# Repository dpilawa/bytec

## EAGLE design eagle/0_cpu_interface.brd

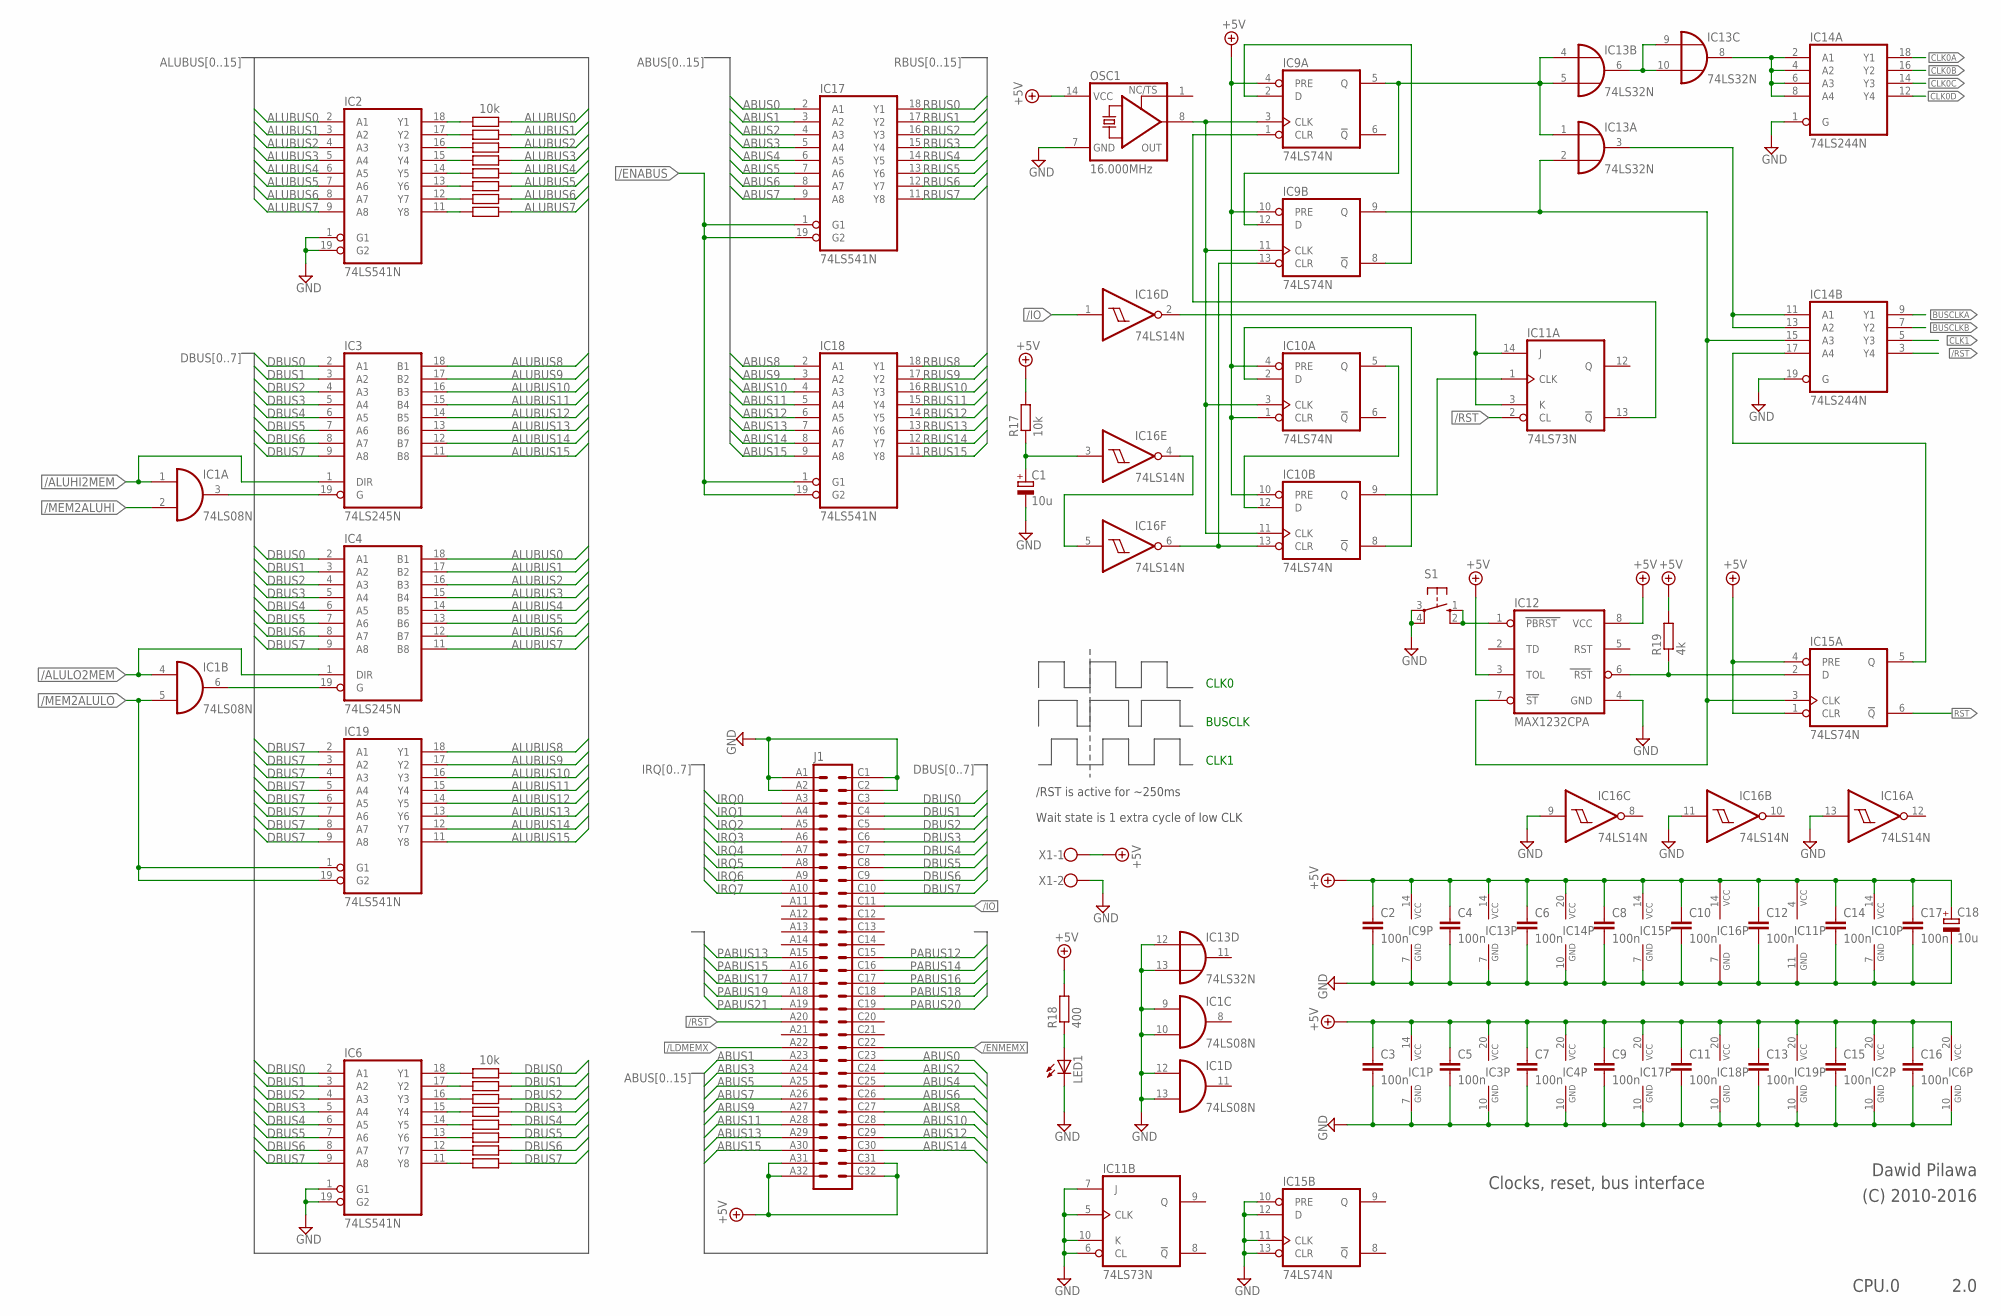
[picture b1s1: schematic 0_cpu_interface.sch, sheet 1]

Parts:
C1: 10u; E2,5-5
C2, C3, C4, C5, C6, C7, C8, C9, C10, C11, C12, C13, C14, C15, C16, C17: 100n; C050-024X044
C18: 10u; E2,5-6
IC1: 74LS08N; DIL14
IC2, IC6, IC17, IC18, IC19: 74LS541N; DIL20
IC3, IC4: 74LS245N; DIL20
IC9, IC10, IC15: 74LS74N; DIL14
IC11: 74LS73N; DIL14
IC12: MAX1232CPA; DIL08
IC13: 74LS32N; DIL14
IC14: 74LS244N; DIL20
IC16: 74LS14N; DIL14
J1: VG64B
LED1: LED5MM
OSC1: 16.000MHz; DIL14S
R1, R9, R17: 10k; 0204/7
R2, R3, R4, R5, R6, R7, R8, R10, R11, R12, R13, R14, R15, R16: R-EU_0204/7; 0204/7
R18: 400; 0204/7
R19: 4k; 0204/7
S1: 10-XX; B3F-10XX
X1: W237-102

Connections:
+5V: C2.1, C3.1, C4.1, C5.1, C6.1, C7.1, C8.1, C9.1, C10.1, C11.1, C12.1, C13.1, C14.1, C15.1, C16.1, C17.1, C18.+, IC1.14 (VCC), IC2.20 (VCC), IC3.20 (VCC), IC4.20 (VCC), IC6.20 (VCC), IC9.4 (PRE), IC9.10 (PRE), IC9.14 (VCC), IC10.1 (CLR), IC10.4 (PRE), IC10.10 (PRE), IC10.14 (VCC), IC11.4 (VCC), IC12.3 (TOL), IC12.8 (VCC), IC13.14 (VCC), IC14.20 (VCC), IC15.1 (CLR), IC15.4 (PRE), IC15.14 (VCC), IC16.14 (VCC), IC17.20 (VCC), IC18.20 (VCC), IC19.20 (VCC), J1.A31, J1.A32, J1.C31, J1.C32, OSC1.14 (VCC), R17.2, R18.2, R19.2, X1.1; also elsewhere on the board
/ALUHI2MEM: IC1.1 (I0), IC3.1 (DIR); also elsewhere on the board
/ALULO2MEM: IC1.4 (I0), IC4.1 (DIR); also elsewhere on the board
/ENABUS: IC17.1 (G1), IC17.19 (G2), IC18.1 (G1), IC18.19 (G2); also elsewhere on the board
/ENMEMX: J1.C22; also elsewhere on the board
/IO: IC16.1 (I), J1.C11; also elsewhere on the board
/LDMEMX: J1.A22; also elsewhere on the board
/MEM2ALUHI: IC1.2 (I1); also elsewhere on the board
/MEM2ALULO: IC1.5 (I1), IC19.1 (G1), IC19.19 (G2); also elsewhere on the board
/RST: IC11.2 (CL), IC14.3 (Y4), J1.A20; also elsewhere on the board
ABUS0: IC17.2 (A1), J1.C23; also elsewhere on the board
ABUS1: IC17.3 (A2), J1.A23; also elsewhere on the board
ABUS2: IC17.4 (A3), J1.C24; also elsewhere on the board
ABUS3: IC17.5 (A4), J1.A24; also elsewhere on the board
ABUS4: IC17.6 (A5), J1.C25; also elsewhere on the board
ABUS5: IC17.7 (A6), J1.A25; also elsewhere on the board
ABUS6: IC17.8 (A7), J1.C26; also elsewhere on the board
ABUS7: IC17.9 (A8), J1.A26; also elsewhere on the board
ABUS8: IC18.2 (A1), J1.C27; also elsewhere on the board
ABUS9: IC18.3 (A2), J1.A27; also elsewhere on the board
ABUS10: IC18.4 (A3), J1.C28; also elsewhere on the board
ABUS11: IC18.5 (A4), J1.A28; also elsewhere on the board
ABUS12: IC18.6 (A5), J1.C29; also elsewhere on the board
ABUS13: IC18.7 (A6), J1.A29; also elsewhere on the board
ABUS14: IC18.8 (A7), J1.C30; also elsewhere on the board
ABUS15: IC18.9 (A8), J1.A30; also elsewhere on the board
ALUBUS0: IC2.2 (A1), IC4.18 (B1), R1.2; also elsewhere on the board
ALUBUS1: IC2.3 (A2), IC4.17 (B2), R2.2; also elsewhere on the board
ALUBUS2: IC2.4 (A3), IC4.16 (B3), R3.2; also elsewhere on the board
ALUBUS3: IC2.5 (A4), IC4.15 (B4), R4.2; also elsewhere on the board
ALUBUS4: IC2.6 (A5), IC4.14 (B5), R5.2; also elsewhere on the board
ALUBUS5: IC2.7 (A6), IC4.13 (B6), R6.2; also elsewhere on the board
ALUBUS6: IC2.8 (A7), IC4.12 (B7), R7.2; also elsewhere on the board
ALUBUS7: IC2.9 (A8), IC4.11 (B8), R8.2; also elsewhere on the board
ALUBUS8: IC3.18 (B1), IC19.18 (Y1); also elsewhere on the board
ALUBUS9: IC3.17 (B2), IC19.17 (Y2); also elsewhere on the board
ALUBUS10: IC3.16 (B3), IC19.16 (Y3); also elsewhere on the board
ALUBUS11: IC3.15 (B4), IC19.15 (Y4); also elsewhere on the board
ALUBUS12: IC3.14 (B5), IC19.14 (Y5); also elsewhere on the board
ALUBUS13: IC3.13 (B6), IC19.13 (Y6); also elsewhere on the board
ALUBUS14: IC3.12 (B7), IC19.12 (Y7); also elsewhere on the board
ALUBUS15: IC3.11 (B8), IC19.11 (Y8); also elsewhere on the board
BUSCLK: IC13.3 (O), IC14.11 (A1), IC14.13 (A2)
BUSCLKA: IC14.9 (Y1); also elsewhere on the board
BUSCLKB: IC14.7 (Y2); also elsewhere on the board
CLK0: IC9.5 (Q), IC9.12 (D), IC13.1 (I0), IC13.4 (I0), IC13.5 (I1)
CLK0A: IC14.18 (Y1); also elsewhere on the board
CLK0B: IC14.16 (Y2); also elsewhere on the board
CLK0C: IC14.14 (Y3); also elsewhere on the board
CLK0D: IC14.12 (Y4); also elsewhere on the board
CLK1: IC14.5 (Y3); also elsewhere on the board
DBUS0: IC3.2 (A1), IC4.2 (A1), IC6.2 (A1), J1.C3, R9.2; also elsewhere on the board
DBUS1: IC3.3 (A2), IC4.3 (A2), IC6.3 (A2), J1.C4, R10.2; also elsewhere on the board
DBUS2: IC3.4 (A3), IC4.4 (A3), IC6.4 (A3), J1.C5, R11.2; also elsewhere on the board
DBUS3: IC3.5 (A4), IC4.5 (A4), IC6.5 (A4), J1.C6, R12.2; also elsewhere on the board
DBUS4: IC3.6 (A5), IC4.6 (A5), IC6.6 (A5), J1.C7, R13.2; also elsewhere on the board
DBUS5: IC3.7 (A6), IC4.7 (A6), IC6.7 (A6), J1.C8, R14.2; also elsewhere on the board
DBUS6: IC3.8 (A7), IC4.8 (A7), IC6.8 (A7), J1.C9, R15.2; also elsewhere on the board
DBUS7: IC3.9 (A8), IC4.9 (A8), IC6.9 (A8), IC19.2 (A1), IC19.3 (A2), IC19.4 (A3), IC19.5 (A4), IC19.6 (A5), IC19.7 (A6), IC19.8 (A7), IC19.9 (A8), J1.C10, R16.2; also elsewhere on the board
GND: C1.-, C2.2, C3.2, C4.2, C5.2, C6.2, C7.2, C8.2, C9.2, C10.2, C11.2, C12.2, C13.2, C14.2, C15.2, C16.2, C17.2, C18.-, IC1.7 (GND), IC1.9 (I0), IC1.10 (I1), IC1.12 (I0), IC1.13 (I1), IC2.1 (G1), IC2.10 (GND), IC2.19 (G2), IC3.10 (GND), IC4.10 (GND), IC6.1 (G1), IC6.10 (GND), IC6.19 (G2), IC9.7 (GND), IC10.7 (GND), IC11.5 (CLK), IC11.6 (CL), IC11.7 (J), IC11.10 (K), IC11.11 (GND), IC12.4 (GND), IC13.7 (GND), IC13.12 (I0), IC13.13 (I1), IC14.1 (G), IC14.10 (GND), IC14.19 (G), IC15.7 (GND), IC15.10 (PRE), IC15.11 (CLK), IC15.12 (D), IC15.13 (CLR), IC16.7 (GND), IC16.9 (I), IC16.11 (I), IC16.13 (I), IC17.10 (GND), IC18.10 (GND), IC19.10 (GND), J1.A1, J1.A2, J1.C1, J1.C2, LED1.K (C), OSC1.7 (GND), S1.3, S1.4 (P1), X1.2; also elsewhere on the board
IRQ0: J1.A3; also elsewhere on the board
IRQ1: J1.A4; also elsewhere on the board
IRQ2: J1.A5; also elsewhere on the board
IRQ3: J1.A6; also elsewhere on the board
IRQ4: J1.A7; also elsewhere on the board
IRQ5: J1.A8; also elsewhere on the board
IRQ6: J1.A9; also elsewhere on the board
IRQ7: J1.A10; also elsewhere on the board
unnamed: IC1.3 (O), IC3.19 (G)
unnamed: IC1.6 (O), IC4.19 (G)
unnamed: IC2.18 (Y1), R1.1
unnamed: IC2.17 (Y2), R2.1
unnamed: IC2.16 (Y3), R3.1
unnamed: IC2.15 (Y4), R4.1
unnamed: IC2.14 (Y5), R5.1
unnamed: IC2.13 (Y6), R6.1
unnamed: IC2.12 (Y7), R7.1
unnamed: IC2.11 (Y8), R8.1
unnamed: IC6.18 (Y1), R9.1
unnamed: IC6.17 (Y2), R10.1
unnamed: IC6.16 (Y3), R11.1
unnamed: IC6.15 (Y4), R12.1
unnamed: IC6.14 (Y5), R13.1
unnamed: IC6.12 (Y7), R15.1
unnamed: IC6.11 (Y8), R16.1
unnamed: IC6.13 (Y6), R14.1
unnamed: IC12.1 (PBRST), S1.1 (S), S1.2 (S1)
unnamed: IC9.3 (CLK), IC9.11 (CLK), IC10.3 (CLK), IC10.11 (CLK), OSC1.8 (OUT)
unnamed: LED1.A, R18.1
unnamed: IC9.2 (D), IC9.8 (!Q)
unnamed: IC14.17 (A4), IC15.5 (Q)
unnamed: IC12.6 (RST), IC15.2 (D), R19.1
unnamed: IC10.2 (D), IC10.8 (!Q)
unnamed: IC13.8 (O), IC14.2 (A1), IC14.4 (A2), IC14.6 (A3), IC14.8 (A4)
unnamed: IC9.1 (CLR), IC11.13 (!Q)
unnamed: C1.+, IC16.3 (I), R17.1
unnamed: IC13.6 (O), IC13.9 (I0), IC13.10 (I1)
unnamed: IC9.9 (Q), IC12.7 (ST), IC13.2 (I1), IC14.15 (A3), IC15.3 (CLK)
unnamed: IC10.5 (Q), IC10.12 (D)
unnamed: IC10.9 (Q), IC11.1 (CLK)
unnamed: IC11.3 (K), IC11.14 (J), IC16.2 (O)
unnamed: IC16.4 (O), IC16.5 (I)
unnamed: IC9.13 (CLR), IC10.13 (CLR), IC16.6 (O)
PABUS12: J1.C15; also elsewhere on the board
PABUS13: J1.A15; also elsewhere on the board
PABUS14: J1.C16; also elsewhere on the board
PABUS15: J1.A16; also elsewhere on the board
PABUS16: J1.C17; also elsewhere on the board
PABUS17: J1.A17; also elsewhere on the board
PABUS18: J1.C18; also elsewhere on the board
PABUS19: J1.A18; also elsewhere on the board
PABUS20: J1.C19; also elsewhere on the board
PABUS21: J1.A19; also elsewhere on the board
RBUS0: IC17.18 (Y1); also elsewhere on the board
RBUS1: IC17.17 (Y2); also elsewhere on the board
RBUS2: IC17.16 (Y3); also elsewhere on the board
RBUS3: IC17.15 (Y4); also elsewhere on the board
RBUS4: IC17.14 (Y5); also elsewhere on the board
RBUS5: IC17.13 (Y6); also elsewhere on the board
RBUS6: IC17.12 (Y7); also elsewhere on the board
RBUS7: IC17.11 (Y8); also elsewhere on the board
RBUS8: IC18.18 (Y1); also elsewhere on the board
RBUS9: IC18.17 (Y2); also elsewhere on the board
RBUS10: IC18.16 (Y3); also elsewhere on the board
RBUS11: IC18.15 (Y4); also elsewhere on the board
RBUS12: IC18.14 (Y5); also elsewhere on the board
RBUS13: IC18.13 (Y6); also elsewhere on the board
RBUS14: IC18.12 (Y7); also elsewhere on the board
RBUS15: IC18.11 (Y8); also elsewhere on the board
RST: IC15.6 (!Q); also elsewhere on the board

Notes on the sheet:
Clocks, reset, bus interface
Dawid Pilawa
(C) 2010-2016
CPU.0
2.0
/RST is active for ~250ms
CLK0
BUSCLK
CLK1
Wait state is 1 extra cycle of low CLK

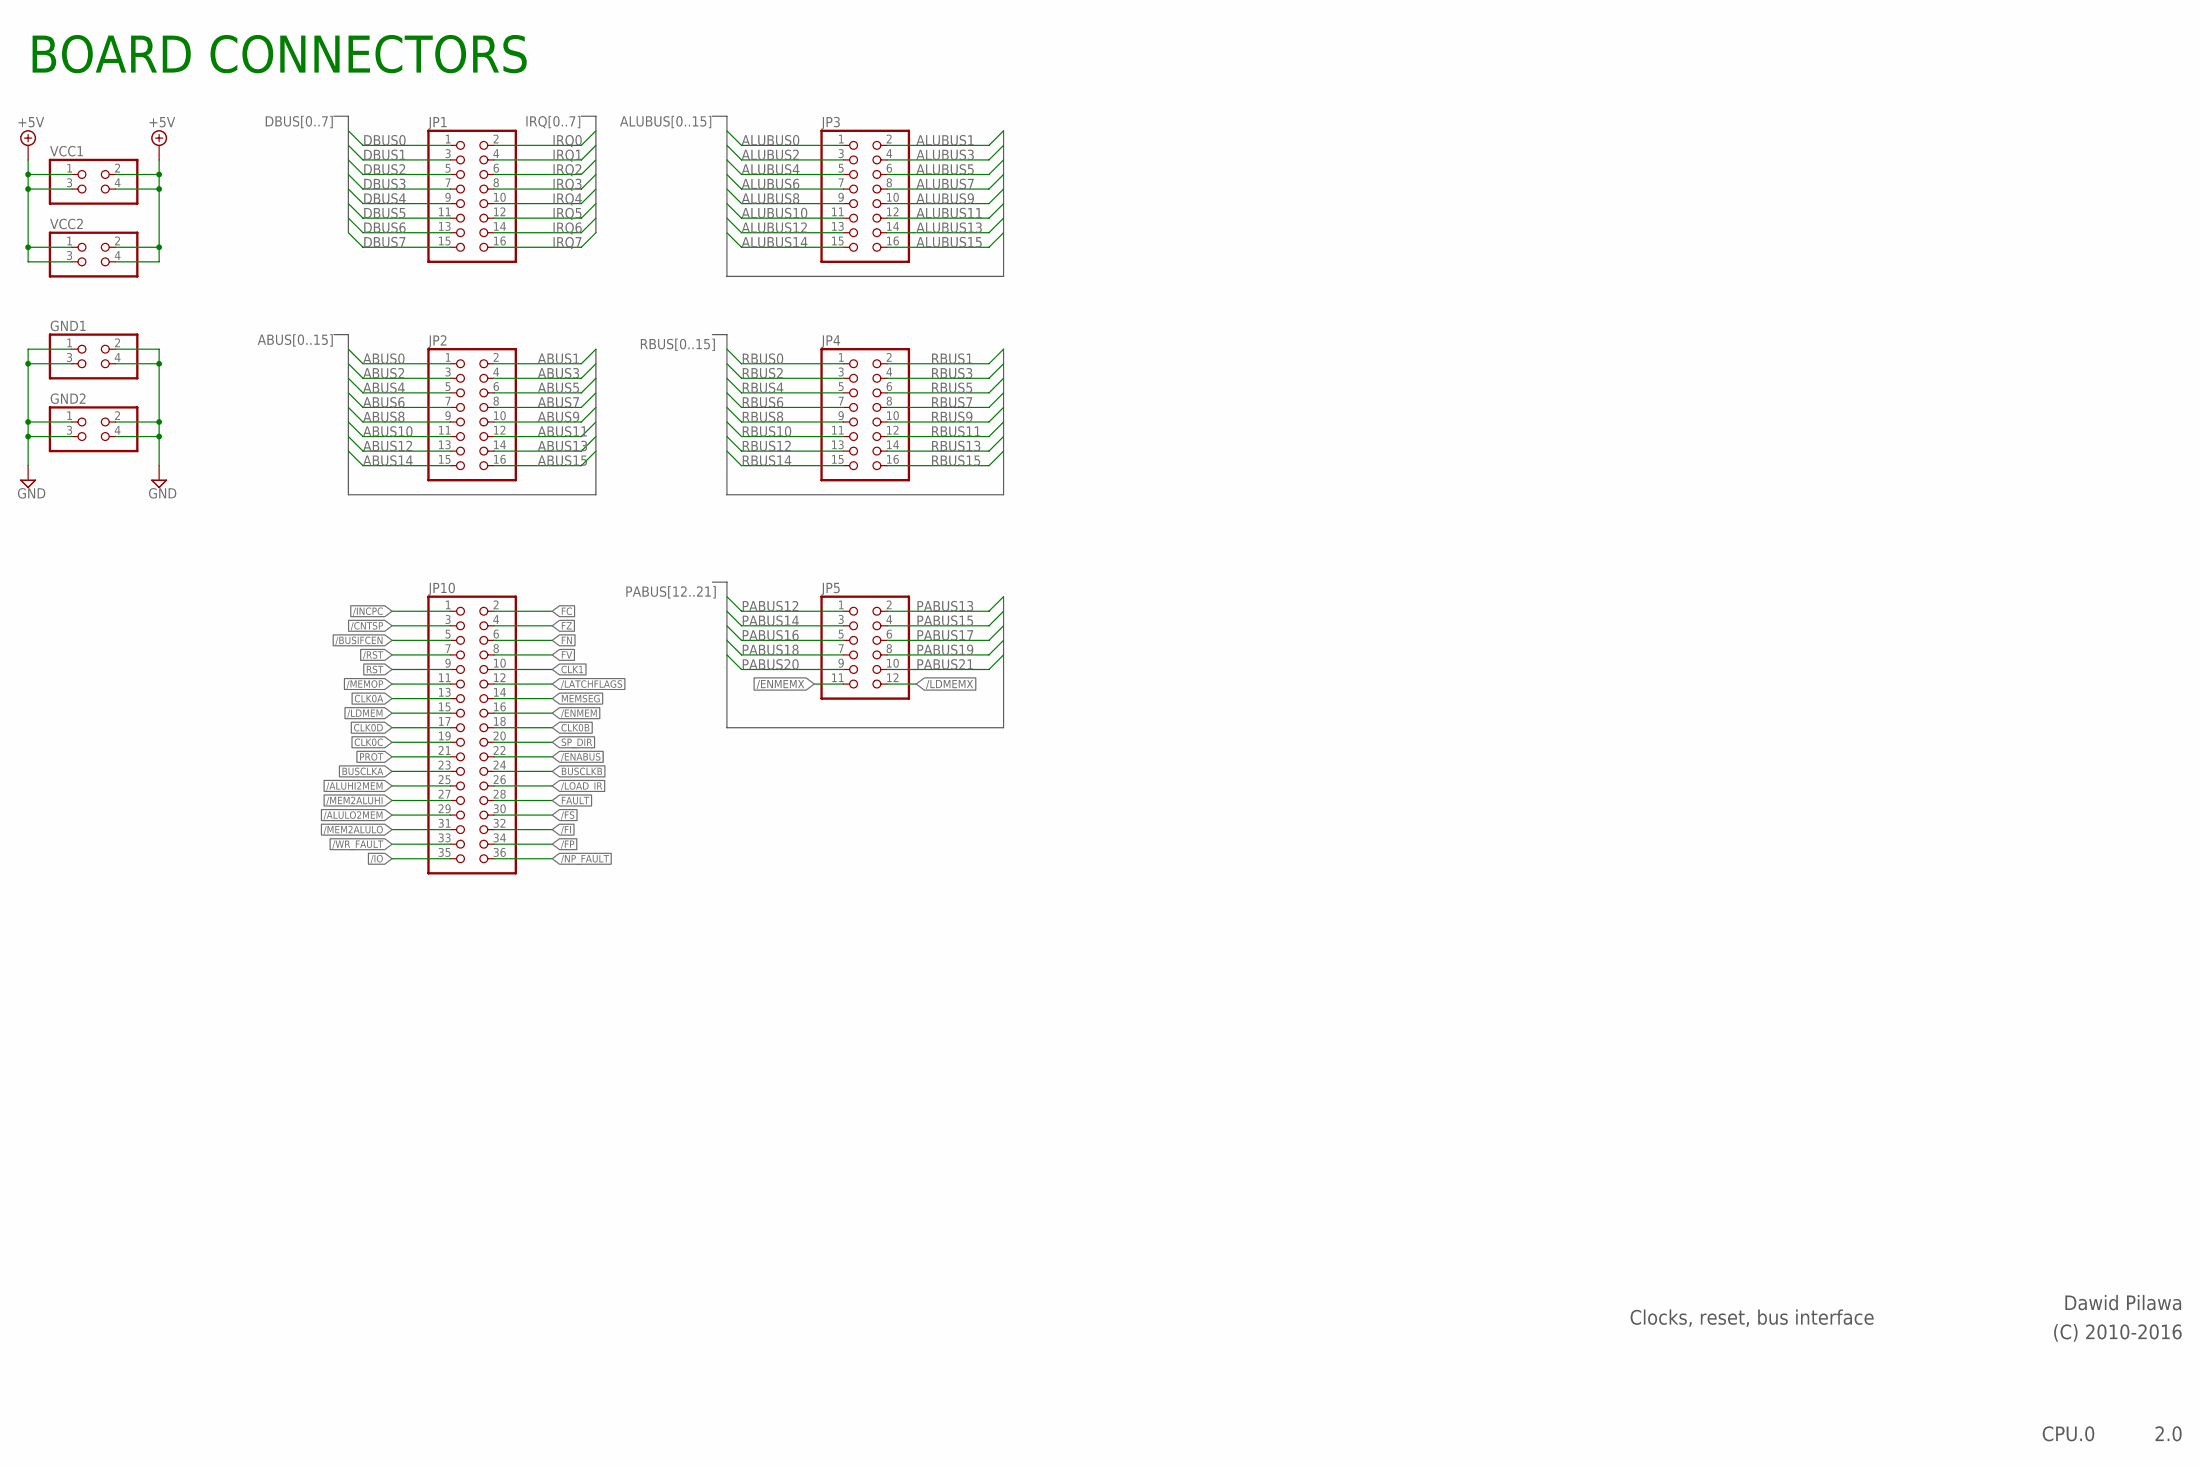
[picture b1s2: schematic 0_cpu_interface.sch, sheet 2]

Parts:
GND1, GND2: PINHD-2X2; 2X02
JP1, JP2, JP3, JP4: PINHD-2X8; 2X08
JP5: PINHD-2X6; 2X06
JP10: PINHD-2X18; 2X18
VCC1, VCC2: PINHD-2X2; 2X02

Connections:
+5V: VCC1.1, VCC1.2, VCC1.3, VCC1.4, VCC2.1, VCC2.2, VCC2.3, VCC2.4; also elsewhere on the board
/ALUHI2MEM: JP10.25; also elsewhere on the board
/ALULO2MEM: JP10.29; also elsewhere on the board
/BUSIFCEN: JP10.5
/CNTSP: JP10.3
/ENABUS: JP10.22; also elsewhere on the board
/ENMEM: JP10.16
/ENMEMX: JP5.11; also elsewhere on the board
/FI: JP10.32
/FP: JP10.34
/FS: JP10.30
/INCPC: JP10.1
/IO: JP10.35; also elsewhere on the board
/LATCHFLAGS: JP10.12
/LDMEM: JP10.15
/LDMEMX: JP5.12; also elsewhere on the board
/LOAD_IR: JP10.26
/MEM2ALUHI: JP10.27; also elsewhere on the board
/MEM2ALULO: JP10.31; also elsewhere on the board
/MEMOP: JP10.11
/NP_FAULT: JP10.36
/RST: JP10.7; also elsewhere on the board
/WR_FAULT: JP10.33
ABUS0: JP2.1; also elsewhere on the board
ABUS1: JP2.2; also elsewhere on the board
ABUS2: JP2.3; also elsewhere on the board
ABUS3: JP2.4; also elsewhere on the board
ABUS4: JP2.5; also elsewhere on the board
ABUS5: JP2.6; also elsewhere on the board
ABUS6: JP2.7; also elsewhere on the board
ABUS7: JP2.8; also elsewhere on the board
ABUS8: JP2.9; also elsewhere on the board
ABUS9: JP2.10; also elsewhere on the board
ABUS10: JP2.11; also elsewhere on the board
ABUS11: JP2.12; also elsewhere on the board
ABUS12: JP2.13; also elsewhere on the board
ABUS13: JP2.14; also elsewhere on the board
ABUS14: JP2.15; also elsewhere on the board
ABUS15: JP2.16; also elsewhere on the board
ALUBUS0: JP3.1; also elsewhere on the board
ALUBUS1: JP3.2; also elsewhere on the board
ALUBUS2: JP3.3; also elsewhere on the board
ALUBUS3: JP3.4; also elsewhere on the board
ALUBUS4: JP3.5; also elsewhere on the board
ALUBUS5: JP3.6; also elsewhere on the board
ALUBUS6: JP3.7; also elsewhere on the board
ALUBUS7: JP3.8; also elsewhere on the board
ALUBUS8: JP3.9; also elsewhere on the board
ALUBUS9: JP3.10; also elsewhere on the board
ALUBUS10: JP3.11; also elsewhere on the board
ALUBUS11: JP3.12; also elsewhere on the board
ALUBUS12: JP3.13; also elsewhere on the board
ALUBUS13: JP3.14; also elsewhere on the board
ALUBUS14: JP3.15; also elsewhere on the board
ALUBUS15: JP3.16; also elsewhere on the board
BUSCLKA: JP10.23; also elsewhere on the board
BUSCLKB: JP10.24; also elsewhere on the board
CLK0A: JP10.13; also elsewhere on the board
CLK0B: JP10.18; also elsewhere on the board
CLK0C: JP10.19; also elsewhere on the board
CLK0D: JP10.17; also elsewhere on the board
CLK1: JP10.10; also elsewhere on the board
DBUS0: JP1.1; also elsewhere on the board
DBUS1: JP1.3; also elsewhere on the board
DBUS2: JP1.5; also elsewhere on the board
DBUS3: JP1.7; also elsewhere on the board
DBUS4: JP1.9; also elsewhere on the board
DBUS5: JP1.11; also elsewhere on the board
DBUS6: JP1.13; also elsewhere on the board
DBUS7: JP1.15; also elsewhere on the board
FAULT: JP10.28
FC: JP10.2
FN: JP10.6
FV: JP10.8
FZ: JP10.4
GND: GND1.1, GND1.2, GND1.3, GND1.4, GND2.1, GND2.2, GND2.3, GND2.4; also elsewhere on the board
IRQ0: JP1.2; also elsewhere on the board
IRQ1: JP1.4; also elsewhere on the board
IRQ2: JP1.6; also elsewhere on the board
IRQ3: JP1.8; also elsewhere on the board
IRQ4: JP1.10; also elsewhere on the board
IRQ5: JP1.12; also elsewhere on the board
IRQ6: JP1.14; also elsewhere on the board
IRQ7: JP1.16; also elsewhere on the board
MEMSEG: JP10.14
PABUS12: JP5.1; also elsewhere on the board
PABUS13: JP5.2; also elsewhere on the board
PABUS14: JP5.3; also elsewhere on the board
PABUS15: JP5.4; also elsewhere on the board
PABUS16: JP5.5; also elsewhere on the board
PABUS17: JP5.6; also elsewhere on the board
PABUS18: JP5.7; also elsewhere on the board
PABUS19: JP5.8; also elsewhere on the board
PABUS20: JP5.9; also elsewhere on the board
PABUS21: JP5.10; also elsewhere on the board
PROT: JP10.21
RBUS0: JP4.1; also elsewhere on the board
RBUS1: JP4.2; also elsewhere on the board
RBUS2: JP4.3; also elsewhere on the board
RBUS3: JP4.4; also elsewhere on the board
RBUS4: JP4.5; also elsewhere on the board
RBUS5: JP4.6; also elsewhere on the board
RBUS6: JP4.7; also elsewhere on the board
RBUS7: JP4.8; also elsewhere on the board
RBUS8: JP4.9; also elsewhere on the board
RBUS9: JP4.10; also elsewhere on the board
RBUS10: JP4.11; also elsewhere on the board
RBUS11: JP4.12; also elsewhere on the board
RBUS12: JP4.13; also elsewhere on the board
RBUS13: JP4.14; also elsewhere on the board
RBUS14: JP4.15; also elsewhere on the board
RBUS15: JP4.16; also elsewhere on the board
RST: JP10.9; also elsewhere on the board
SP_DIR: JP10.20

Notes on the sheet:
Clocks, reset, bus interface
Dawid Pilawa
(C) 2010-2016
CPU.0
2.0
BOARD CONNECTORS

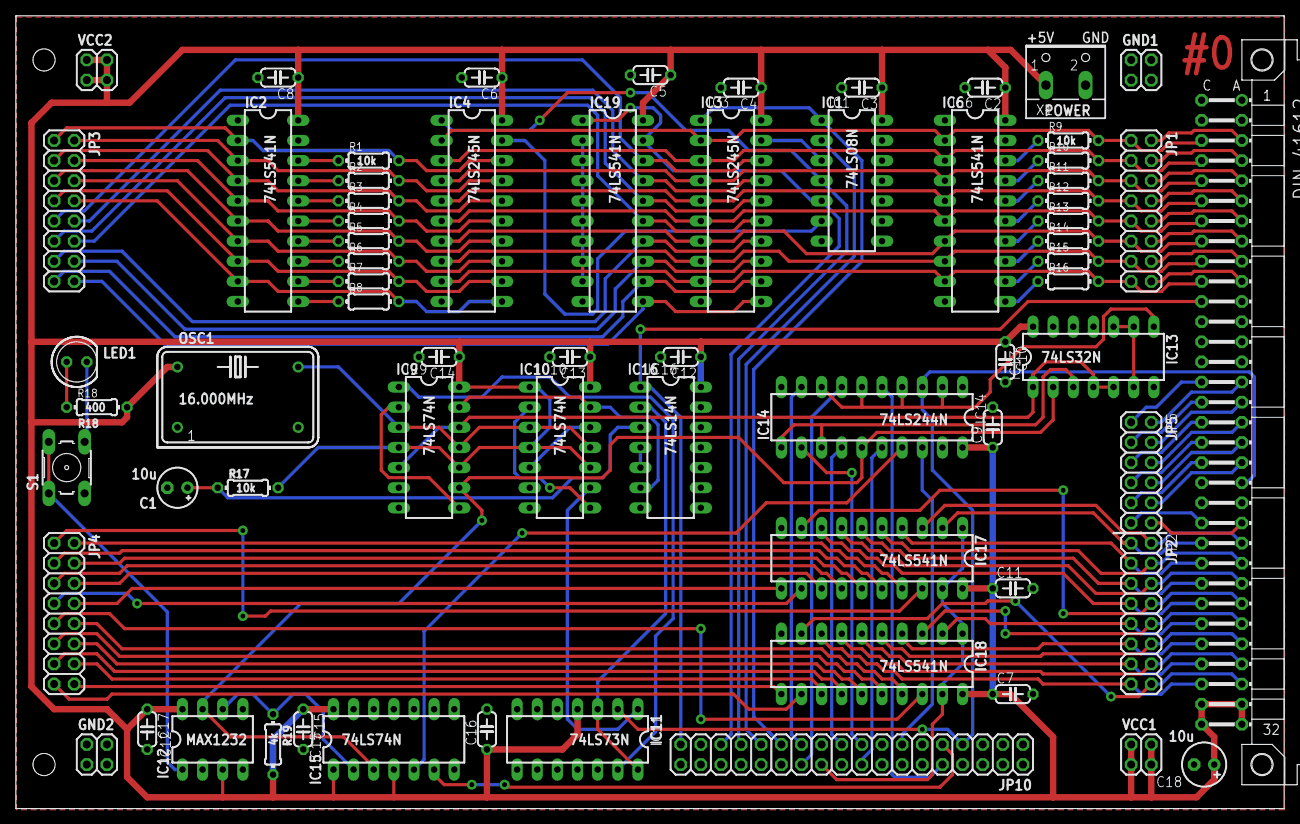
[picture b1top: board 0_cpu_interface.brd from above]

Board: 2 copper layers, 160.0 x 100.0 mm, 68 parts (0 on the bottom side), 130 nets.

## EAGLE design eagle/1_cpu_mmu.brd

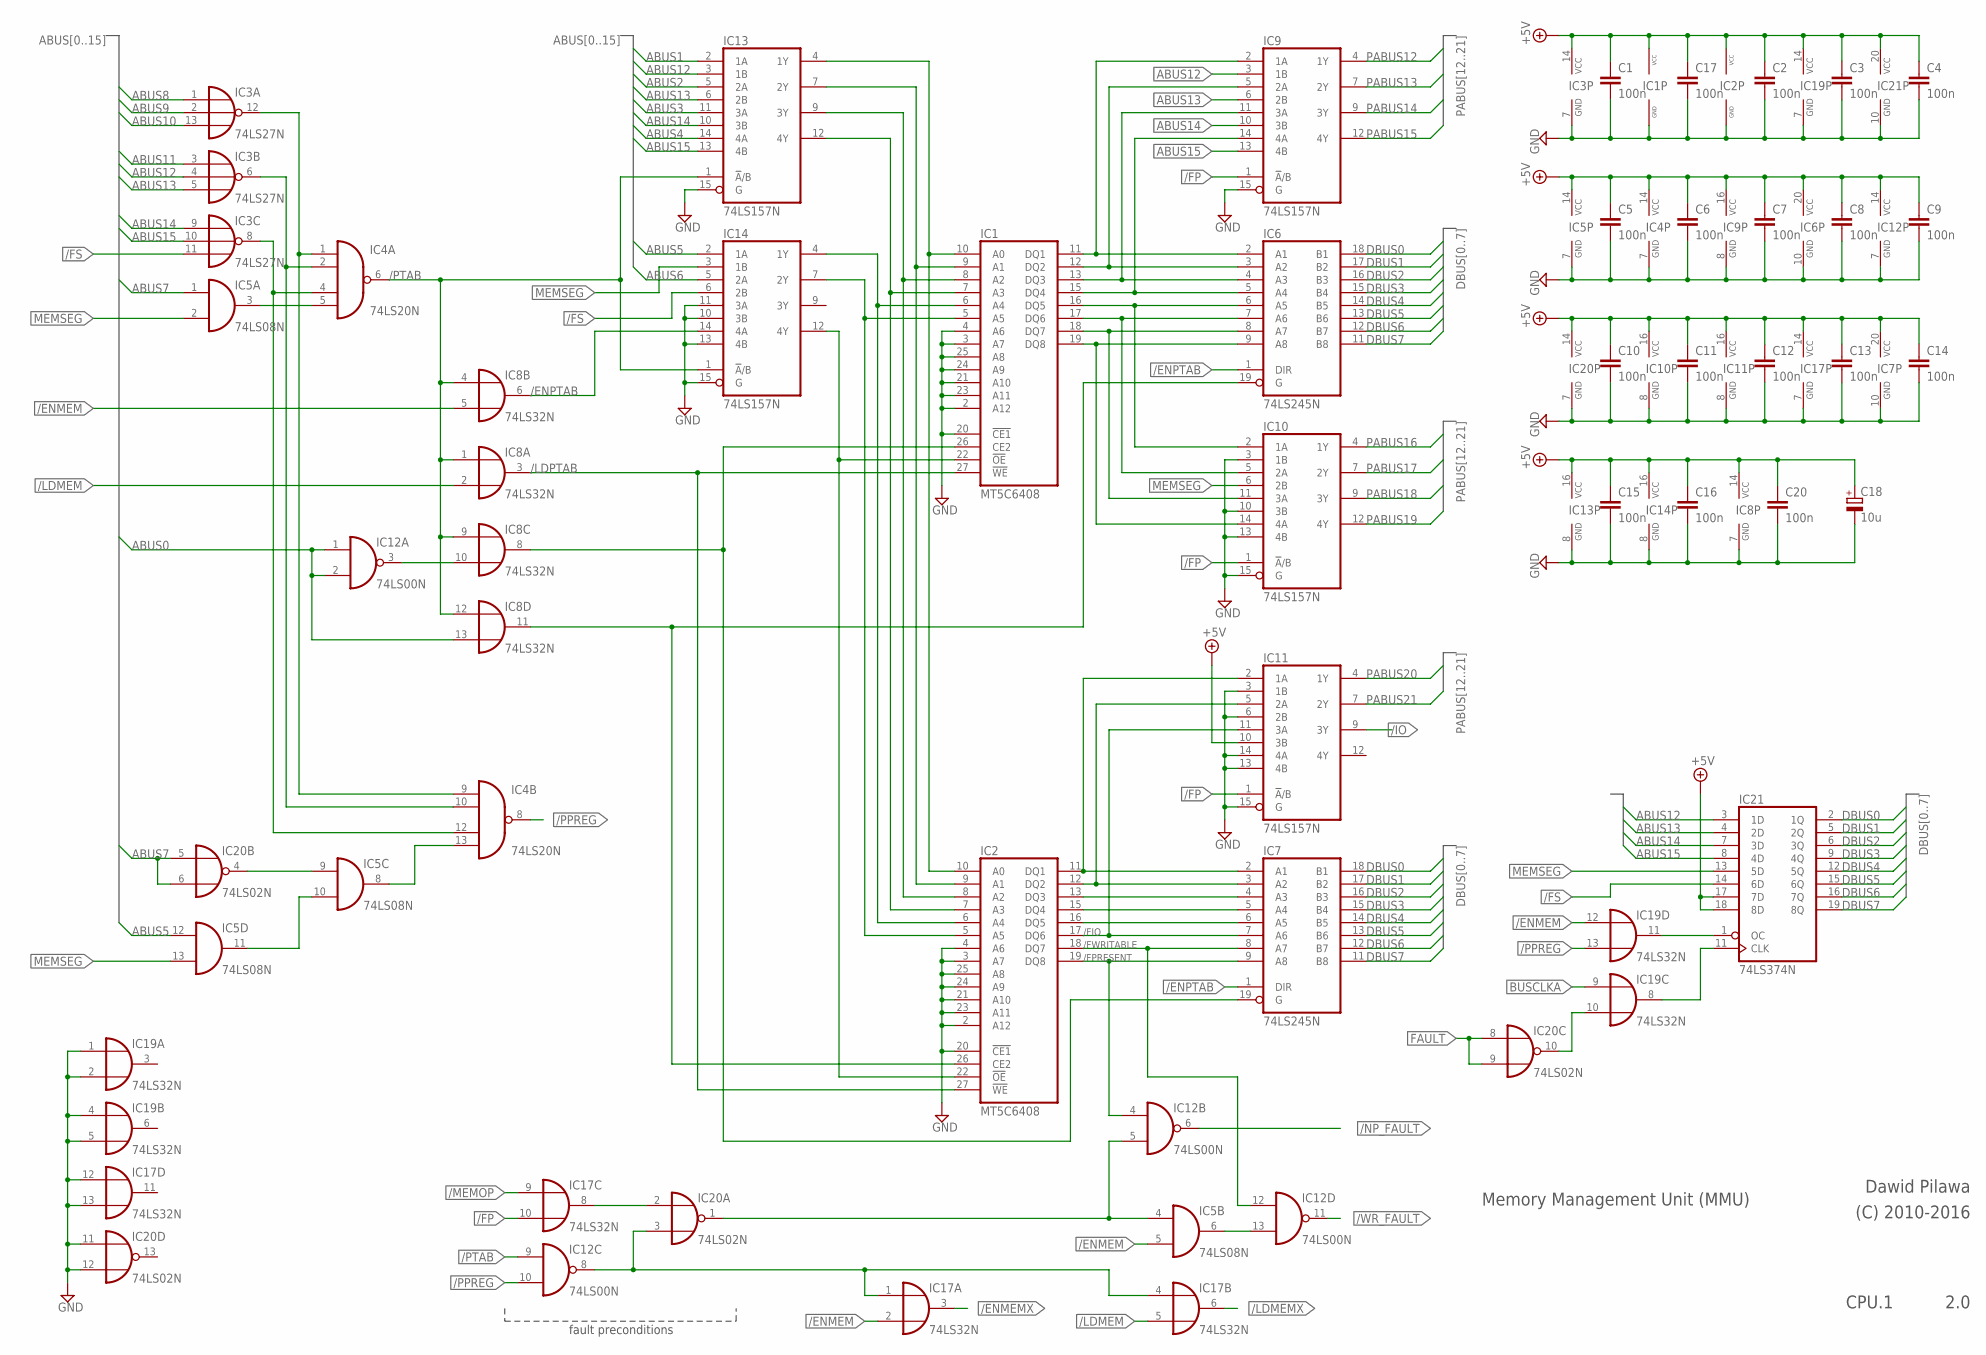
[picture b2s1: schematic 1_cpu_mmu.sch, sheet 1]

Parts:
C1, C2, C3, C4, C5, C6, C7, C8, C9, C10, C11, C12, C13, C14, C15, C16, C17, C20: 100n; C050-024X044
C18: 10u; E2,5-6
IC1, IC2: MT5C6408; DIL28-3
IC3: 74LS27N; DIL14
IC4: 74LS20N; DIL14
IC5: 74LS08N; DIL14
IC6, IC7: 74LS245N; DIL20
IC8, IC17, IC19: 74LS32N; DIL14
IC9, IC10, IC11, IC13, IC14: 74LS157N; DIL16
IC12: 74LS00N; DIL14
IC20: 74LS02N; DIL14
IC21: 74LS374N; DIL20

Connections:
+5V: C1.1, C2.1, C3.1, C4.1, C5.1, C6.1, C7.1, C8.1, C9.1, C10.1, C11.1, C12.1, C13.1, C14.1, C15.1, C16.1, C17.1, C18.+, C20.1, IC1.28 (VCC), IC2.28 (VCC), IC3.14 (VCC), IC4.14 (VCC), IC5.14 (VCC), IC6.20 (VCC), IC7.20 (VCC), IC8.14 (VCC), IC9.16 (VCC), IC10.16 (VCC), IC11.10 (3B), IC11.16 (VCC), IC12.14 (VCC), IC13.16 (VCC), IC14.16 (VCC), IC17.14 (VCC), IC19.14 (VCC), IC20.14 (VCC), IC21.17 (7D), IC21.18 (8D), IC21.20 (VCC); also elsewhere on the board
/ENMEM: IC5.5 (I1), IC8.5 (I1), IC17.2 (I1), IC19.12 (I0); also elsewhere on the board
/ENMEMX: IC17.3 (O); also elsewhere on the board
/ENPTAB: IC6.1 (DIR), IC7.1 (DIR), IC8.6 (O), IC14.14 (4A)
/FIO: IC2.17 (DQ6), IC7.7 (A6), IC11.11 (3A)
/FP: IC9.1 (!A!/B), IC10.1 (!A!/B), IC11.1 (!A!/B), IC17.10 (I1); also elsewhere on the board
/FPRESENT: IC2.19 (DQ8), IC7.9 (A8), IC12.4 (I0)
/FS: IC3.11 (I2), IC14.6 (2B), IC21.14 (6D); also elsewhere on the board
/FWRITABLE: IC2.18 (DQ7), IC7.8 (A7), IC12.12 (I0)
/IO: IC11.9 (3Y); also elsewhere on the board
/LDMEM: IC8.2 (I1), IC17.5 (I1); also elsewhere on the board
/LDMEMX: IC17.6 (O); also elsewhere on the board
/LDPTAB: IC1.27 (!WE), IC2.27 (!WE), IC8.3 (O)
/MEMOP: IC17.9 (I0); also elsewhere on the board
/NP_FAULT: IC12.6 (O); also elsewhere on the board
/PPREG: IC4.8 (O), IC12.10 (I1), IC19.13 (I1)
/PTAB: IC4.6 (O), IC8.1 (I0), IC8.4 (I0), IC8.9 (I0), IC8.12 (I0), IC12.9 (I0), IC13.1 (!A!/B), IC14.1 (!A!/B)
/WR_FAULT: IC12.11 (O); also elsewhere on the board
ABUS0: IC8.13 (I1), IC12.1 (I0), IC12.2 (I1); also elsewhere on the board
ABUS1: IC13.2 (1A); also elsewhere on the board
ABUS2: IC13.5 (2A); also elsewhere on the board
ABUS3: IC13.11 (3A); also elsewhere on the board
ABUS4: IC13.14 (4A); also elsewhere on the board
ABUS5: IC5.12 (I0), IC14.2 (1A); also elsewhere on the board
ABUS6: IC14.5 (2A); also elsewhere on the board
ABUS7: IC5.1 (I0), IC20.5 (I0), IC20.6 (I1); also elsewhere on the board
ABUS8: IC3.1 (I0); also elsewhere on the board
ABUS9: IC3.2 (I1); also elsewhere on the board
ABUS10: IC3.13 (I2); also elsewhere on the board
ABUS11: IC3.3 (I0); also elsewhere on the board
ABUS12: IC3.4 (I1), IC9.3 (1B), IC13.3 (1B), IC21.3 (1D); also elsewhere on the board
ABUS13: IC3.5 (I2), IC9.6 (2B), IC13.6 (2B), IC21.4 (2D); also elsewhere on the board
ABUS14: IC3.9 (I0), IC9.10 (3B), IC13.10 (3B), IC21.7 (3D); also elsewhere on the board
ABUS15: IC3.10 (I1), IC9.13 (4B), IC13.13 (4B), IC21.8 (4D); also elsewhere on the board
BUSCLKA: IC19.9 (I0); also elsewhere on the board
DBUS0: IC6.18 (B1), IC7.18 (B1), IC21.2 (1Q); also elsewhere on the board
DBUS1: IC6.17 (B2), IC7.17 (B2), IC21.5 (2Q); also elsewhere on the board
DBUS2: IC6.16 (B3), IC7.16 (B3), IC21.6 (3Q); also elsewhere on the board
DBUS3: IC6.15 (B4), IC7.15 (B4), IC21.9 (4Q); also elsewhere on the board
DBUS4: IC6.14 (B5), IC7.14 (B5), IC21.12 (5Q); also elsewhere on the board
DBUS5: IC6.13 (B6), IC7.13 (B6), IC21.15 (6Q); also elsewhere on the board
DBUS6: IC6.12 (B7), IC7.12 (B7), IC21.16 (7Q); also elsewhere on the board
DBUS7: IC6.11 (B8), IC7.11 (B8), IC21.19 (8Q); also elsewhere on the board
FAULT: IC20.8 (I0), IC20.9 (I1); also elsewhere on the board
GND: C1.2, C2.2, C3.2, C4.2, C5.2, C6.2, C7.2, C8.2, C9.2, C10.2, C11.2, C12.2, C13.2, C14.2, C15.2, C16.2, C17.2, C18.-, C20.2, IC1.2 (A12), IC1.3 (A7), IC1.4 (A6), IC1.14 (GND), IC1.20 (!CE1), IC1.21 (A10), IC1.23 (A11), IC1.24 (A9), IC1.25 (A8), IC2.2 (A12), IC2.3 (A7), IC2.4 (A6), IC2.14 (GND), IC2.20 (!CE1), IC2.21 (A10), IC2.23 (A11), IC2.24 (A9), IC2.25 (A8), IC3.7 (GND), IC4.7 (GND), IC5.7 (GND), IC6.10 (GND), IC7.10 (GND), IC8.7 (GND), IC9.8 (GND), IC9.15 (G), IC10.3 (1B), IC10.8 (GND), IC10.10 (3B), IC10.13 (4B), IC10.15 (G), IC11.3 (1B), IC11.6 (2B), IC11.8 (GND), IC11.13 (4B), IC11.14 (4A), IC11.15 (G), IC12.7 (GND), IC13.8 (GND), IC13.15 (G), IC14.8 (GND), IC14.10 (3B), IC14.11 (3A), IC14.13 (4B), IC14.15 (G), IC17.7 (GND), IC17.12 (I0), IC17.13 (I1), IC19.1 (I0), IC19.2 (I1), IC19.4 (I0), IC19.5 (I1), IC19.7 (GND), IC20.7 (GND), IC20.11 (I0), IC20.12 (I1), IC21.10 (GND); also elsewhere on the board
MEMSEG: IC5.2 (I1), IC5.13 (I1), IC10.6 (2B), IC14.3 (1B), IC21.13 (5D); also elsewhere on the board
unnamed: IC3.12 (O), IC4.1 (I0), IC4.9 (I0)
unnamed: IC3.6 (O), IC4.2 (I1), IC4.10 (I1)
unnamed: IC5.9 (I0), IC20.4 (O)
unnamed: IC4.5 (I3), IC5.3 (O)
unnamed: IC1.11 (DQ1), IC6.2 (A1), IC9.2 (1A)
unnamed: IC1.12 (DQ2), IC6.3 (A2), IC9.5 (2A)
unnamed: IC1.13 (DQ3), IC6.4 (A3), IC9.11 (3A)
unnamed: IC1.15 (DQ4), IC6.5 (A4), IC9.14 (4A)
unnamed: IC1.16 (DQ5), IC6.6 (A5), IC10.2 (1A)
unnamed: IC1.17 (DQ6), IC6.7 (A6), IC10.5 (2A)
unnamed: IC1.18 (DQ7), IC6.8 (A7), IC10.11 (3A)
unnamed: IC1.19 (DQ8), IC6.9 (A8), IC10.14 (4A)
unnamed: IC2.11 (DQ1), IC7.2 (A1), IC11.2 (1A)
unnamed: IC2.12 (DQ2), IC7.3 (A2), IC11.5 (2A)
unnamed: IC2.13 (DQ3), IC7.4 (A3)
unnamed: IC2.15 (DQ4), IC7.5 (A4)
unnamed: IC2.16 (DQ5), IC7.6 (A5)
unnamed: IC17.8 (O), IC20.2 (I0)
unnamed: IC1.10 (A0), IC2.10 (A0), IC13.4 (1Y)
unnamed: IC1.9 (A1), IC2.9 (A1), IC13.7 (2Y)
unnamed: IC1.8 (A2), IC2.8 (A2), IC13.9 (3Y)
unnamed: IC1.7 (A3), IC2.7 (A3), IC13.12 (4Y)
unnamed: IC1.6 (A4), IC2.6 (A4), IC14.4 (1Y)
unnamed: IC1.5 (A5), IC2.5 (A5), IC14.7 (2Y)
unnamed: IC1.26 (CE2), IC7.19 (G), IC8.8 (O)
unnamed: IC2.26 (CE2), IC6.19 (G), IC8.11 (O)
unnamed: IC1.22 (!OE), IC2.22 (!OE), IC14.12 (4Y)
unnamed: IC8.10 (I1), IC12.3 (O)
unnamed: IC12.8 (O), IC17.1 (I0), IC17.4 (I0), IC20.3 (I1)
unnamed: IC5.4 (I0), IC12.5 (I1), IC20.1 (O)
unnamed: IC5.6 (O), IC12.13 (I1)
unnamed: IC5.10 (I1), IC5.11 (O)
unnamed: IC3.8 (O), IC4.4 (I2), IC4.12 (I2)
unnamed: IC4.13 (I3), IC5.8 (O)
unnamed: IC19.10 (I1), IC20.10 (O)
unnamed: IC19.8 (O), IC21.11 (CLK)
unnamed: IC19.11 (O), IC21.1 (OC)
PABUS12: IC9.4 (1Y); also elsewhere on the board
PABUS13: IC9.7 (2Y); also elsewhere on the board
PABUS14: IC9.9 (3Y); also elsewhere on the board
PABUS15: IC9.12 (4Y); also elsewhere on the board
PABUS16: IC10.4 (1Y); also elsewhere on the board
PABUS17: IC10.7 (2Y); also elsewhere on the board
PABUS18: IC10.9 (3Y); also elsewhere on the board
PABUS19: IC10.12 (4Y); also elsewhere on the board
PABUS20: IC11.4 (1Y); also elsewhere on the board
PABUS21: IC11.7 (2Y); also elsewhere on the board

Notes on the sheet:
Memory Management Unit (MMU)
Dawid Pilawa
(C) 2010-2016
CPU.1
2.0
fault preconditions

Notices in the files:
sim/Devices.h:
Copyright 2010, 2011 Dawid Pilawa
This program is free software: you can redistribute it and/or modify
it under the terms of the GNU General Public License as published by
the Free Software Foundation, either version 3 of the License, or
(at your option) any later version.
